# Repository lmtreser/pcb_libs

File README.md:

# PCB LIBs

Bibliotecas para el diseño de PCBs con los componentes más utilizados en los trabajos prácticos de las escuelas EEST N°3 y EEST N°5 de la ciudad de Mar del Plata. Además se incluyen bibliotecas para otros programas CAD que pueden ser útil en el diseño o en la generación de documentación.

La ultima versión se puede descargar desde el repositorio [en este enlace](https://github.com/lmtreser/pcb_libs/).

- `/EAGLE/treser_lib.lbr` Biblioteca compatible con Autodesk EAGLE v7 y superior.
- `/KiCad/Treser.3dshapes` Modelos 3D compatibles con KiCad v7.
- `/KiCad/Treser.pretty` Footprints compatibles con KiCad v7.
- `/KiCad/Treser.symbols` Symbols compatibles con KiCad v7.
- `/FidoCadJ/circuitos` Circuitos varios dibujados con FidoCadJ.
- `/FidoCadJ/ejemplos` Ejemplos varios dibujados con FidoCadJ.
- `/FidoCadJ/libs` Bibliotecas para FidoCadJ.
- `/Fritzing/parts` Bibliotecas para Fritzing.

#### Autodesk EAGLE

**EAGLE** (siglas de Easily Applicable Graphical Layout Editor) es un programa de diseño de diagramas y PCBs con autoenrutador famoso alrededor del mundo, debido a la gran cantidad de bibliotecas de componentes alrededor de la red. Autodesk Inc. adquirió a la empresa desarrolladora original, CadSoft Computer GmbH en 2016. Más en [Wikipedia](https://es.m.wikipedia.org/wiki/EAGLE)

La última versión es la *9.6.2* y se puede descargar desde el sitio [Autodesk Legacy Software Versions](http://eagle.autodesk.com/eagle/software-versions/).

#### KiCad EDA

**KiCad** es un paquete de software libre para la automatización del diseño electrónico (del inglés: Electronic Design Automation, EDA). Facilita el diseño de esquemáticos para circuitos electrónicos y su conversión a placa de circuito impreso. KiCad fue desarrollado originalmente por Jean-Pierre Charras. Cuenta con un entorno integrado para captura esquemática y de diseño de PCB. Existen herramientas dentro del software para crear una lista de materiales, ilustraciones, archivos Gerber y vistas 3D de la PCB y sus componentes. Más en [Wikipedia](https://es.m.wikipedia.org/wiki/KiCad).

La última versión de KiCad se puede descargar desde el sitio oficial [KiCad EDA](https://www.kicad.org/).

#### Fritzing

**Fritzing** es un programa libre de automatización de diseño electrónico que busca ayudar a diseñadores y artistas para que puedan pasar de prototipos (usando, por ejemplo, placas de pruebas) a productos finales. Fritzing fue creado bajo los principios de Processing y Arduino, y permite a los diseñadores, artistas, investigadores y aficionados documentar sus prototipos basados en Arduino y crear esquemas de circuitos impresos para su posterior fabricación. Además, cuenta con un sitio web complementario que ayuda a compartir y discutir bosquejos y experiencias y a reducir los costos de fabricación. Más en [Wikipedia](https://es.m.wikipedia.org/wiki/Fritzing).

La última versión de Fritzing se puede descargar desde el [sitio oficial](https://fritzing.org/download/).

#### FidoCadJ

**FidoCadJ** es un editor gráfico vectorial para GNU/Linux, MacOSX, Windows y Android creado por el profesor Davide Bucci. Se distribuye bajo licencia GPL3 de forma gratuita, es muy liviano y se puede utilizar con distintos fines. Posee una gran colección de símbolos y footprints para electrónica y electricidad.

La última versión de FidoCadJ se puede descargar desde el [sitio oficial](http://darwinne.github.io/FidoCadJ/index.html).

## Recursos

- Autodesk EAGLE
  - [Vídeo Tutoriales EAGLE v7](https://drive.google.com/drive/folders/1XGSJn0cd9M4ImH0A7ExIwCd90hmlcn3g)
  - [Vídeo Tutoriales EAGLE v8](https://drive.google.com/drive/folders/1uMNlElwInSr0HR45rr7a-xuvfVmWcQN1)
  - [Vídeo Tutoriales EAGLE v9](https://drive.google.com/drive/folders/1IOiAV6nzpNvacRHGGPwNLOrX68K4Gx2w)
  - [SparkFun Electronics Eagle Libraries](https://github.com/sparkfun/SparkFun-Eagle-Libraries)
  - [Adafruit Eagle Library](https://github.com/adafruit/Adafruit-Eagle-Library)
  - [UltraLibrarian](https://www.ultralibrarian.com/cad-vendors/eagle/)
  - [SnapMagic EAGLE](https://www.snapeda.com/eagle/)
  - [Autodesk Library.io](https://library.io/)
  - [Logos, dibujos y simbolos en EAGLE](https://www.automatismos-mdq.com.ar/blog/2011/07/logos-dibujos-y-simbolos-en-eagle.html)

- KiCad EDA
  - [KiCad Libraries](https://kicad.github.io/)
  - [SparkFun Electronics KiCad Libraries](https://github.com/sparkfun/SparkFun-KiCad-Libraries)
  - [SnapMagic KiCad](https://www.snapeda.com/kicad/)
  - [Digi-Key KiCad Library](https://github.com/Digi-Key/digikey-kicad-library)
  - [Performing A Circuit Simulation In KiCad](https://www.woolseyworkshop.com/2019/07/01/performing-a-circuit-simulation-in-kicad/)
  - [KiCanvas](https://blog.thea.codes/introducing-kicanvas/)
  - [CI/CD with KiCad and Gitlab](https://sschueller.github.io/posts/ci-cd-with-kicad-and-gitlab/)
  - [Pinion — Nice-looking interactive diagrams for KiCAD PCBs](https://yaqwsx.github.io/Pinion/)

- Fritzing
  - [Fritzing](https://fritzing.org/)
  - [AdaFruit Fritzing Library](https://github.com/adafruit/Fritzing-Library)
  - [Sparkfun Fritzing Parts](https://github.com/sparkfun/Fritzing_Parts)
  - [Cómo crear componentes personalizados para Fritzing](https://www.automatismos-mdq.com.ar/blog/2020/04/como-crear-componentes-personalizados-para-fritzing.html)

- FidoCadJ
  - [FidoCadJ](https://darwinne.github.io/FidoCadJ/)
  - [Editor gráfico FidoCadJ](https://www.automatismos-mdq.com.ar/blog/2020/06/editor-grafico-fidocadj.html)
  
- Otros Recursos
  - [Compendio de ánexos técnicos](https://drive.google.com/drive/folders/1JNl1bw6pRH7ckWr4CoAMkLXcyVetzXd8)
  - [GrabCAD, free CAD files](https://grabcad.com/library)
  - [Ngspice, open source spice simulator](https://ngspice.sourceforge.io/)

## Licencia

Este trabajo está protegido por la **Licencia MIT**. Puedes acceder a la versión original de la licencia (en inglés) a través del archivo [LICENSE](./LICENSE) o en línea en [The MIT License (MIT)](https://mit-license.org/). También proporcionamos una traducción no oficial desde [Wikipedia](https://es.m.wikipedia.org/wiki/Licencia_MIT#La_licencia):

Copyright (c) 2024 Lucas Martín Treser

Por la presente se concede permiso, libre de cargos, a cualquier persona que obtenga una copia de este software y de los archivos de documentación asociados (el "Software"), a utilizar el Software sin restricción, incluyendo sin limitación los derechos a usar, copiar, modificar, fusionar, publicar, distribuir, sublicenciar, y/o vender copias del Software, y a permitir a las personas a las que se les proporcione el Software a hacer lo mismo, sujeto a las siguientes condiciones:

El aviso de copyright anterior y este aviso de permiso se incluirán en todas las copias o partes sustanciales del Software.

EL SOFTWARE SE PROPORCIONA "COMO ESTÁ", SIN GARANTÍA DE NINGÚN TIPO, EXPRESA O IMPLÍCITA, INCLUYENDO PERO NO LIMITADO A GARANTÍAS DE COMERCIALIZACIÓN, IDONEIDAD PARA UN PROPÓSITO PARTICULAR E INCUMPLIMIENTO. EN NINGÚN CASO LOS AUTORES O PROPIETARIOS DE LOS DERECHOS DE AUTOR SERÁN RESPONSABLES DE NINGUNA RECLAMACIÓN, DAÑOS U OTRAS RESPONSABILIDADES, YA SEA EN UNA ACCIÓN DE CONTRATO, AGRAVIO O CUALQUIER OTRO MOTIVO, DERIVADAS DE, FUERA DE O EN CONEXIÓN CON EL SOFTWARE O SU USO U OTRO TIPO DE ACCIONES EN EL SOFTWARE.

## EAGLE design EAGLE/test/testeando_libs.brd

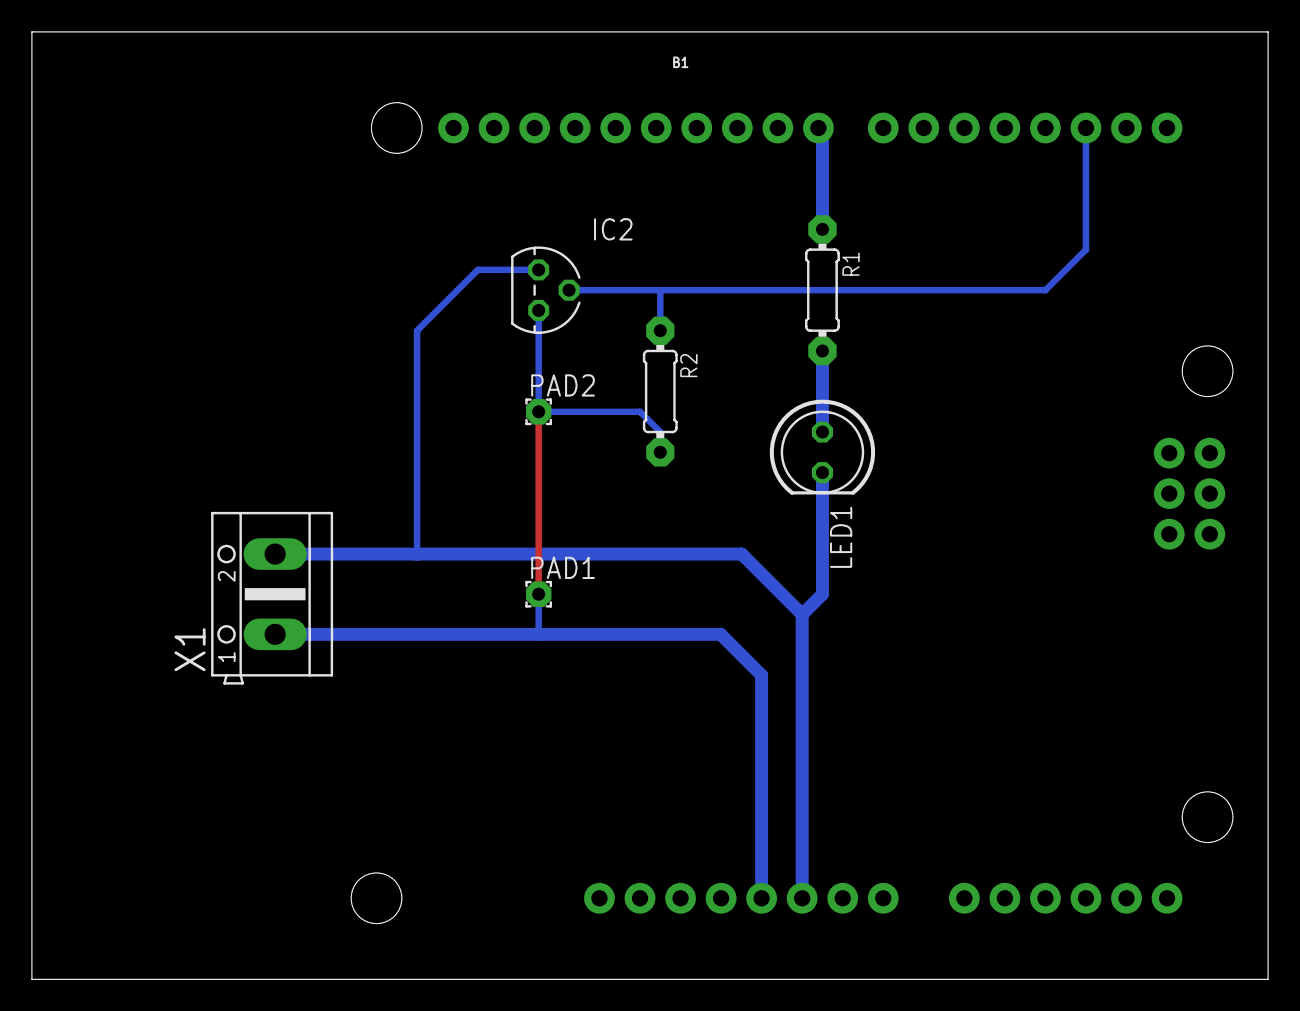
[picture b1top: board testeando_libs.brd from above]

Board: 2 copper layers, 77.5 x 59.4 mm, 9 parts (0 on the bottom side), 5 nets.

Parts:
B1: ARDUINO_UNO_R3; ARDUINO_R3
IC2: DS18B20; TO92
LED1: LED5MM
PAD1, PAD2: 1,6/0,8
R1: 330; 0204/7
R2: 4k7; 0204/7
U$1: LOGO_EEST_N5; LOGO_EEST_N5_PAC_250
X1: PWR; AK500/2

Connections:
GND: B1.GND@1, IC2.3, LED1.K, X1.2
unnamed: B1.D8, R1.1
unnamed: LED1.A, R1.2
unnamed: B1.D2, IC2.2, R2.1
VCC: B1.5V, IC2.1, PAD1.1, PAD2.1, R2.2, X1.1

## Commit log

2023-11-11 eagle lib
2023-11-13 Agregado logos EEST N°3 y N°5
2023-11-13 Proyecto de ejemplo
2023-11-13 Agregados nuevos componentes
2023-12-01 Nuevos componentes NE567, BC557, CNY70
2023-12-04 Plantilla Proyecto EAGLE v7
2023-12-04 Plantilla Proyecto EAGLE v9
2023-12-04 Plantilla Sketch Arduino
2024-01-10 Actualizar README.md
2024-01-13 add KiCad v7 libs
2024-01-15 organizacion de directorios
2024-01-15 update KiCad libs
2024-02-01 Update LICENSE
2024-02-04 add fidocadj circuits
2024-02-04 add fidocadj libs
2024-02-04 add fidocadj ejemplos
2024-02-04 add frtizing parts
2024-02-04 update fritzing parts
2024-02-04 update kicad 3d shapes
2024-02-04 update kicad pretty
2024-02-04 add kicad symbols
2024-02-05 update docs
2024-02-05 add screenshots
2024-05-08 add ESP-01S module 3d model
2024-05-09 add ESP-01 module
2024-05-15 add Fritzing Parts: USB
2024-05-16 add rs-485 module
2024-05-25 add Arduino Nano MicroUSB
2024-06-14 add estándar de fabricación
2024-10-16 add PCB Cheatsheet
2025-01-06 add thermal guide
2025-01-28 add articles from lcamtuf.substack.com
2025-03-07 add soldadura/desoldadura
2025-04-11 add magnetic sensor
2025-04-11 add pn532 parts
2025-04-11 add neopixels parts
2025-04-18 mv docs
2025-04-18 add technical datasheets
2025-08-29 add new kicad components
